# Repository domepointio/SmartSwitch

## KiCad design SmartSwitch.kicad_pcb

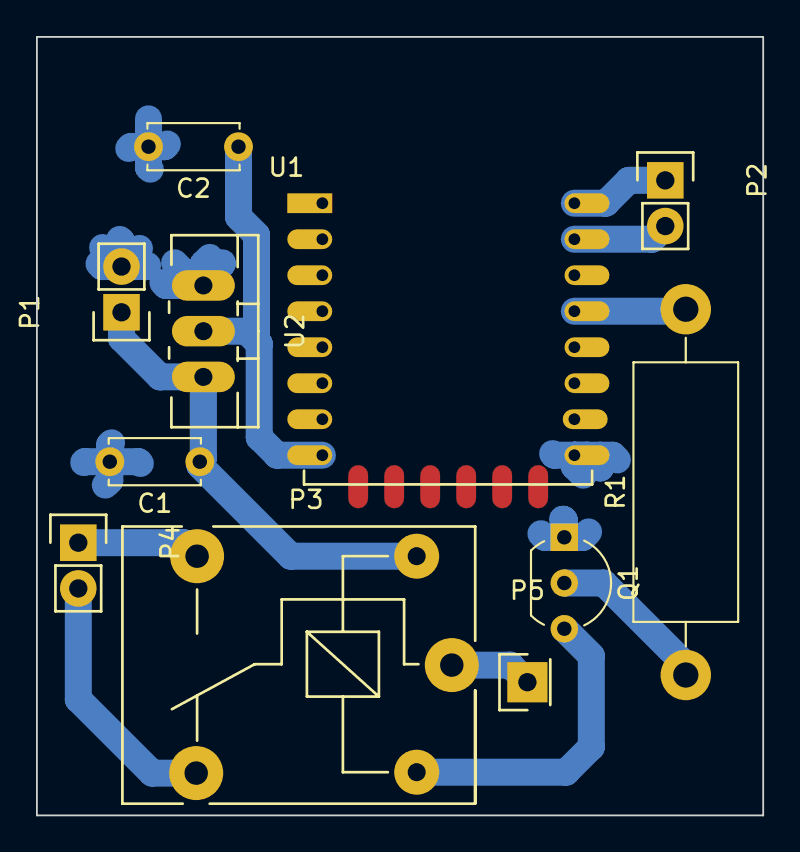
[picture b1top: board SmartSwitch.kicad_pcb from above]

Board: 2 copper layers, 40.4 x 43.2 mm, 11 parts (0 on the bottom side), 11 nets.

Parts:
C1, C2: C; C_Disc_D5.0mm_W2.5mm_P5.00mm
P1, P2, P4: CONN_01X02; Socket_Strip_Straight_1x02
P3: CONN_01X05; Relay_SANYOU_SRD_Series_Form_C
P5: CONN_01X01; Socket_Strip_Straight_1x01
Q1: PN2222A; TO-92_Inline_Wide
R1: R; R_Axial_DIN0614_L14.3mm_D5.7mm_P20.32mm_Horizontal
U1: ESP-12E
U2: LM1117-3.3; TO-220_Neutral123_Vertical_LargePads

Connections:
/Colector: P3.5, Q1.3
/Con1: P3.3, P4.1
/Con2: P3.4, P4.2
/GPIO04: R1.2, U1.13
/Out: P3.1, P5.1
/Vin: C1.1, P1.1, P3.2, U2.3
/Vout: C2.1, U1.8, U2.2
GND: C1.2, C2.2, P1.2, Q1.1, U1.9, U2.1
unnamed: P2.1, U1.16
unnamed: P2.2, U1.15
unnamed: Q1.2, R1.1

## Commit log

2017-01-17 SmartSwitch
